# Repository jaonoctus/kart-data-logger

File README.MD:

# ESP32 Kart Telemetry System

A telemetry and datalogging system for open-track go-karts, built around a single
steering-wheel-mounted ESP32 display board that handles everything: GPS
acquisition, lap timing, dashboard rendering and SD logging.

> **Note:** earlier revisions of this project split the work between a
> helmet-mounted logger node and the display, linked over ESP-NOW. That helmet
> node proved unreliable at the track and has been removed — the display is now
> the only node.

## System Architecture

Single target: the **Display Dashboard Node**.

* **Board:** JC3248W535N (ESP32-S3, AXS15231B QSPI panel)
* **Role:** GPS acquisition, lap detection, UI dashboard, and SD logging.
* **Features:**
  * GPS from ATGM336 (default) or u-blox M9, wired directly to the board.
  * Live speed, G-force, satellite count and display battery state.
  * Finish-line based lap detection with best/previous lap deltas.
  * Telemetry logged to SD card per recording session.
  * Optional MPU6050 IMU for speed filtering and steering angle.

### Build targets in `platformio.ini`

Both targets build the same application (`src/main_display.cpp`) and differ only
in the panel driver backend:

* `env:display_gfx` — Arduino_GFX backend (`lib/DisplayGFX`). **Default.**
* `env:display` — esp_lcd backend (`lib/DisplayBSP`). Fallback.

The Arduino_GFX backend is the default because it resolves a QSPI panel wedge
seen with the esp_lcd path.

## Key Technical Features

* **Modular GPS provider** abstraction in `GpsManager`.
* **Finish-line lap detection** in `LapManager`, driven by GPS position.
* **`fix_stride.py` prebuild patch** for SquareLine Studio LVGL 9 image exports.
* **Display-wedge watchdog** — a 5s task watchdog on `loopTask` turns a panel
  wedge into a fast auto-reset instead of a permanent freeze.
* **Charge mode** to keep the board from eating the charger's current budget.
* **Optional IMU support** to improve speed filtering and live telemetry.

## Charge mode

The charger's current is shared between the board and the cell, so a running
dashboard slows charging considerably. Charge mode parks the device:

* Stops the recording session and closes the GPS UART.
* Drops the CPU to 80 MHz (the floor for stable USB-CDC — don't go lower).
* Swaps to a minimal charge screen and blanks the backlight after 15s.

It is **only ever entered manually**, from the `CHARGE MODE` button on the
config screen. Nothing enters it automatically, so bench testing and debugging
are unaffected.

While parked: tap anywhere to wake the backlight and read the battery for
another 15s; press `RESUME` to leave. Resuming re-probes the GPS, which takes a
couple of seconds.

> **Whether the GPS actually sleeps depends on which one is fitted.** Charge mode
> calls `gps.standby()` and leaves the UART open so `wake()` can talk to it.
> On the **ATGM336** that is a quiesce, not a sleep: the RF front end has no
> software power-down at all, so it keeps drawing ~25-40 mA and standby only cuts
> it to GPS-only at 1Hz with NMEA muted. On the **u-blox M9** it is a real
> power-down — `UBX-RXM-PMREQ` software backup, woken by traffic on the module's
> RX pin. Coming back may cost a cold start if the module's V_BCKP does not hold
> the BBR, but the configuration itself is in flash and survives either way.

> **The percentage reads high while charging.** With no power-path charger the
> sense divider sits on the charger rail, so it measures the cell terminal
> voltage *under charge*, which is well above its resting value — expect a
> jump downward when you unplug. It's shown as `~94%` to mark it approximate;
> the voltage below it is the number to trust.

The charge screen and the config-screen button are both built at runtime in
`lib/UiHelper/uiHelper.cpp` rather than exported from SquareLine, so
re-exporting `lib/ui/` will not wipe them.

## Hardware Requirements

* JC3248W535N display board
* GPS module wired to `RX=6` / `TX=7` — ATGM336, or a u-blox M9 such as the Matek
  M9N-5883. The ATGM336 runs on 3V3; the M9N-5883 wants 4~5.5V, so its VCC belongs
  on the IP5306 5V rail, not the board's 3V3.
* Optional MPU6050 IMU
* microSD card formatted FAT32

## Software Dependencies

Built with PlatformIO.

* `lvgl/lvgl` (v9.x)
* `moononournation/GFX Library for Arduino` (`display_gfx` only)
* `mikalhart/TinyGPSPlus`
* `ElectronicCats/MPU6050`

## GPS Providers

`GpsManager` supports two providers. Nothing older than these is supported — the
NEO-6M-era 9600-baud fallback is gone.

* **ATGM336 provider** (current default)
  * Enabled with `-D GPS_PROVIDER_ATGM336`.
  * 10Hz.
  * Configured over CASIC text commands (`$PCAS`), which are never acked, so the
    module cannot report whether a setting took. It also cannot be put to sleep:
    `$PCAS12` standby is a 5L-only feature and this is a 5N.
* **u-blox M9 provider** — targets the M9 generation (NEO-M9N), e.g. the Matek
  M9N-5883.
  * Leave `-D GPS_PROVIDER_ATGM336` out of the build flags.
  * 25Hz.
  * Probes 115200 then 38400 (the M9 default), and moves the port to 115200.
  * Sleeps for real in charge mode — `UBX-RXM-PMREQ` software backup, armed to
    wake on UART RX traffic.
  * Configured over binary UBX, which *is* acked, and the provider reads the
    dynamic model / rate / power mode back at boot and logs `BEFORE:` and
    `AFTER:` lines. Legacy `UBX-CFG-*` messages are deprecated on generation 9
    but still supported; they are removed on generation 10, so a future module
    means porting `configureUblox()` to `UBX-CFG-VALSET`.
  * **Speaks `UBX-NAV-PVT`, not NMEA.** All NMEA output is disabled. One 92-byte
    frame per epoch carries position at 1e-7° (~1.1cm), Doppler ground speed,
    UTC, `numSV`, `fixType`, `pDOP`, `hAcc` and `sAcc` — less traffic than
    GGA+RMC and strictly more information, as one coherent snapshot instead of a
    position from one sentence stitched to a speed from another. It also makes the
    four-constellation problem vanish: per-system duplication of GSA/GSV was an
    NMEA artefact, and UBX has no talker IDs to multiply.
  * `hasFix()` therefore uses the receiver's own verdict — `gnssFixOK`,
    `fixType == 3`, and `hAcc` within bounds — rather than the `sats >= 4 &&
    HDOP <= 3` heuristic the NMEA path had to guess with.
  * **TinyGPSPlus is unused on this path.** It stays in `lib_deps` for the
    ATGM336, and static-archive linking drops it (and the unreferenced provider)
    from the image. It is still compiled every build, so a break in either
    provider still fails the build.

The flag lives in `[display_common] -> build_flags_base`, so it applies to both
build targets at once.

### Fix rate

ATGM336 runs at **10Hz**, u-blox M9 at **25Hz** — the receiver's ceiling with all
four constellations. GGA+RMC at 25Hz is ~36kbaud of the 115200 the port is set to,
so the link has room to spare. 40ms epochs also land on exact centisecond values
(`.00`/`.04`/`.08`…), which matters because NMEA timestamps are centiseconds and
anything finer would round.

The rate buys **log resolution**, which is the point — at 100 km/h, 25Hz puts a
sample every 1.1m instead of every 2.8m. It buys much less for lap times, because
`LapManager` intersects the finish gate with the segment between consecutive fixes
and interpolates the crossing millisecond along it, so the reported time never
quantised to the fix interval in the first place.

To sustain 25Hz, `LogManager` holds the log file open for the whole session and
`flush()`es once a second, rather than reopening and closing it per row (25 FAT
directory updates a second is where a slow card starts stalling). The trade is
durability: an abrupt power-off now costs up to a second of the lap instead of a
single sample. The telemetry queue is 40 frames for the same reason — ~1.6s of
headroom at 25Hz, so a card stall doesn't drop rows.

### GPS wiring

The GPS UART pins are set by `GPS_STANDALONE_RX` / `GPS_STANDALONE_TX` in
`[display_common]`, currently `6` and `7`.

Watch for collisions when changing these: `GPIO5` carries the battery sense
divider (`DISPLAY_BATT_ADC` in `src/main_display.cpp`), and `GPIO18`/`GPIO17`
are the IMU's I2C pins when `ENABLE_IMU` is set.

## Filesystem & Storage

The display reads and writes to a **FAT32 microSD** card. No files need to be
pre-populated — the display creates what it needs on first boot — but the files
below may be edited on a computer for configuration.

#### `/config.ini` (auto-created)

Stores display preferences. Created with defaults on first boot if absent.

```ini
# Kart Data Logger Configuration
theme=dark          # dark | light
selected_track=0    # index into tracks.ini
```

#### `/health.csv` (auto-created, only when something goes wrong)

Appended across every session, one row per second in which the telemetry queue
had no room for a frame:

```
epoch,log,dropped_total,dropped_delta
```

**An empty or absent file is the good news** — it means no row was ever lost. Any
row in it means the card could not keep up with the fix rate and the matching
`log_N.csv` is missing samples, so the file is worth checking after a race rather
than watching the serial log, which is unreachable with the dash on a wheel.

`epoch` comes from the GPS-synced system clock, so it lines up with the `epoch`
column in the telemetry file; before the first fix it degrades to uptime.

#### `/tracks.ini` (optional, user-created)

Defines named tracks with GPS finish-line coordinates. The display reads this at
boot and populates the track selector in the UI. If absent, no tracks are
preloaded.

```ini
# Kart track configurations
count=2

0_name=Kartódromo Granja Viana
0_left_lat=-23.60488969
0_left_lon=-46.83622658
0_right_lat=-23.60493793
0_right_lon=-46.83641597

1_name=My Track
1_left_lat=0.00000000
1_left_lon=0.00000000
1_right_lat=0.00000000
1_right_lon=0.00000000
```

#### `/log_N.csv` (auto-created per session)

Telemetry session logs. A new numbered file is created each time a recording
session starts.

```
epoch,speed,totalGForce,gForceX,gForceY,steering_angle,sats,lat,lng,fix,pdop,hacc,sacc
```

The last four are the receiver's report on its own fix, and are **zero on the
ATGM336** — NMEA carries no equivalent, so zero means "not reported", not "perfect".

| column | meaning |
| --- | --- |
| `fix`  | `0` no fix, `2` 2D, `3` 3D, `5` time only. Never `1`/`4` (dead reckoning) — that is NEO-M9V silicon, not M9N. |
| `pdop` | position dilution of precision |
| `hacc` | horizontal accuracy estimate, metres, ~1σ |
| `sacc` | speed accuracy estimate, m/s |

`hacc` is the useful one for analysis: it does not make a position better, it tells
you which samples to distrust. Around 0.7-1.5m under open sky, climbing near
buildings and in the first seconds after a cold start. A lap time interpolated
between two 12m samples is not a lap time to trust to hundredths.

These columns are **appended**, never inserted, so everything in `tools/` keeps
working — those read by column name or by a fixed `sscanf` prefix. A CSV derived
from GoPro footage simply lacks them.

Note `lat`/`lng` are written at 7 decimal places (~1.1cm) rather than 6 (~11cm),
which is what `UBX-NAV-PVT` actually resolves.

## Setup & Installation

1. Clone this repository.
2. Open it in VSCode with PlatformIO.
3. Edit the UI using the SquareLine Studio project files in `UIDesign/`.
4. Export the UI to `/lib/ui/` and let `fix_stride.py` patch LVGL image metadata during build.
5. Flash the firmware: `tools/flash.sh` (see below).
6. Insert a FAT32 microSD card into the display. A default `config.ini` is created on first boot.

### Flashing

`upload_port` in `platformio.ini` is pinned to `/dev/cu.usbmodem1101`, which is one
machine's enumeration — the same board comes up under a different name elsewhere and
`pio run -t upload` then fails on a port that isn't there. `tools/flash.sh` finds the
board by USB `VID:PID` instead and passes it with `--upload-port`, which overrides the
pinned value:

```bash
tools/flash.sh              # default env, confirm, then upload
tools/flash.sh -m           # ...and open the serial monitor afterwards
tools/flash.sh -e display   # the esp_lcd fallback env
tools/flash.sh -p /dev/cu.usbmodem101   # skip discovery
tools/flash.sh -y           # no confirmation prompt (also FLASH_YES=1)
tools/flash.sh -- -v        # anything after -- goes to `pio run`
```

Before uploading it prints the port, env and `FW_VERSION`, and warns if the tree is
dirty — `FW_VERSION` is `git describe --tags --always --dirty` and shows on the setup
screen, so it is easy to flash uncommitted edits by accident. If more than one board is
attached it lists the candidates and asks for `-p`.

`pio run -e display_gfx -t upload` still works if the pinned port happens to be right.

## Dormant libraries

These libraries are no longer part of the build — nothing includes them — but
they are kept in `lib/` because they may be useful again:

* `EspNowManager` + `Shared/EspNowProtocol.h` message types — the board-to-board radio link.
* `ErrorLogManager` — LittleFS error capture and transfer.
* `AudioManager`, `VoiceParser` — I2S playback and spoken number/lap announcements.
* `PowerManager` — button-driven hibernate and power gating.
* `FakeGps` — CSV replay for development without GPS hardware.

`Shared/EspNowProtocol.h` is still compiled: `TelemetryMsg` is the record the
display passes between the UI, the lap manager and the SD log task.

## Design files

Design files are included under the `hardware/` folder.

### 3D Models

I've used Fusion to design 3D models for the custom enclosures and mounts. These
are located in `hardware/3d-models/` and exported as `.f3d` and `.3mf` files.
You can open and modify these in Fusion or any compatible 3D modeling software.

## Visual Reference

The repository includes module photos in the `images/` folder.

## Notes

* The display firmware owns the whole pipeline: GPS, lap timing, UI and SD logging.
* Lap detection only runs while a recording session is active.

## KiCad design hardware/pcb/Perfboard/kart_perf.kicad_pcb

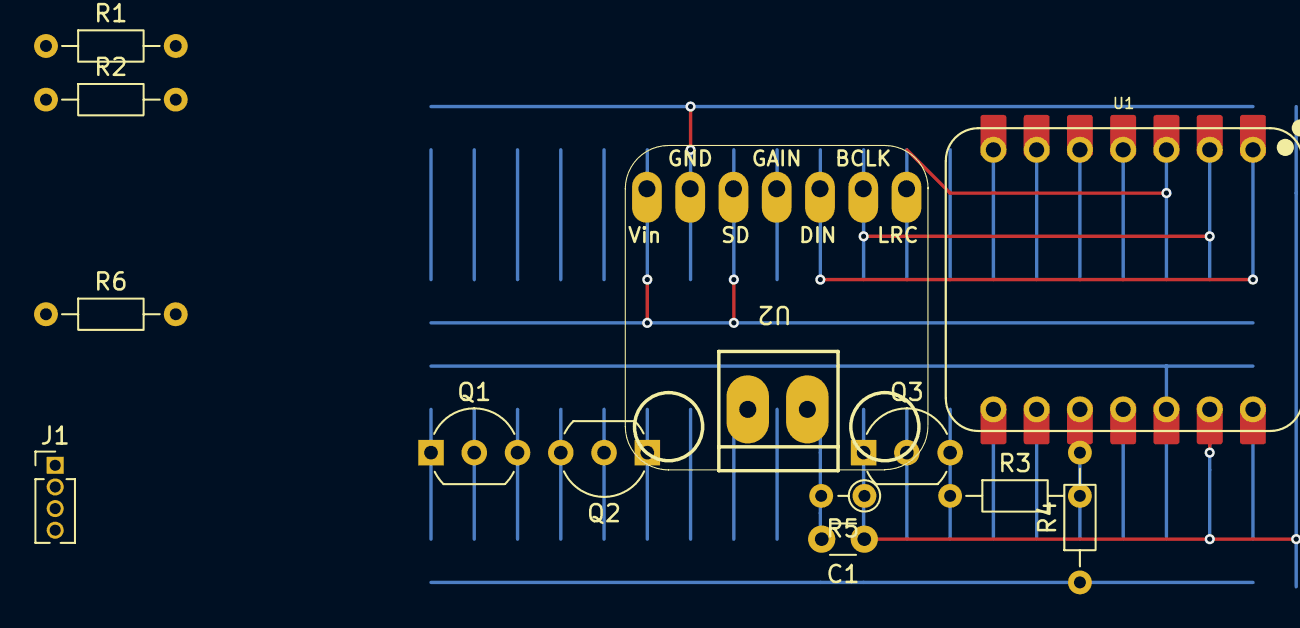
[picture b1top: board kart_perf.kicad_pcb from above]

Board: 2 copper layers, 13 parts (0 on the bottom side), 16 nets.

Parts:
C1: 0.1uf; C_Disc_D3.0mm_W1.6mm_P2.50mm
J1: Conn_01x04_Pin; PinHeader_1x04_P1.27mm_Vertical
Q1: BC327; TO-92_Inline_Wide
Q2, Q3: 2N3904; TO-92_Inline_Wide
R1, R3, R6: 10k; R_Axial_DIN0204_L3.6mm_D1.6mm_P7.62mm_Horizontal
R2: 470; R_Axial_DIN0204_L3.6mm_D1.6mm_P7.62mm_Horizontal
R4: 1M; R_Axial_DIN0204_L3.6mm_D1.6mm_P7.62mm_Horizontal
R5: 1M; R_Axial_DIN0204_L3.6mm_D1.6mm_P2.54mm_Vertical
U1: XIAO-ESP32-S3-SMD; XIAO-ESP32-S3-DIP
U2: adafruit-MAX98357

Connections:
+3.3V: Q1.3 (E), R1.2, U1.12 (3V3)
/BATT_EN: R6.2, U1.11 (GPIO9_A10_D10_MOSI)
/PERIF_EN: R3.1, U1.4 (GPIO4_A3_D3)
/SENSE: C1.2, R4.2, R5.2, U1.10 (GPIO8_A9_D9_MISO)
/V_PERIF: J1.3, Q1.1 (C), U2.1 (Vin), U2.3 (~SD_MODE)
GND: J1.4, Q2.1 (E), Q3.1 (E), U1.13 (GND), U2.2 (GND)
unnamed: J1.1, U1.7 (GPIO43_D6_TX)
unnamed: J1.2, U1.8 (GPIO44_D7_RX)
unnamed: Q1.2 (B), R1.1, R2.1
unnamed: Q2.2 (B), R3.2
unnamed: Q2.3 (C), R2.2
unnamed: Q3.2 (B), R6.1
unnamed: C1.1, Q3.3 (C), R5.1
unnamed: U1.1 (GPIO1_A0_D0), U2.5 (DIN)
unnamed: U1.2 (GPIO2_A1_D1), U2.6 (BCLK)
unnamed: U1.3 (GPIO3_A2_D2), U2.7 (LRC)

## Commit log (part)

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2026-06-25 AudioManager: stop safelly before hibernation
2026-06-25 BatteryManager: enhance button logic
2026-06-25 PowerManager: enhance button logic
2026-06-25 pcb: add perfboard circuit
